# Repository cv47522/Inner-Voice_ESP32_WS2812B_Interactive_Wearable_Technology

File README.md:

# Inner Voice

- Wearable Technology and Functional Wear Study Project.
- Materials: ESP32 / Flora RGB Smart NeoPixel / Conductive Fabrics & Yarns
- Language: Arduino
- **More details of the project (Demo Video): https://wantinghsieh.com/inner-voice**

---

## Build

**[Link to the documentation page.](https://fabacademy.wantinghsieh.com/assignment/16-wildcard-week)**

## Belt Controller

## Bracelet Controller

## WS2812B Trianguler Light Modules

---

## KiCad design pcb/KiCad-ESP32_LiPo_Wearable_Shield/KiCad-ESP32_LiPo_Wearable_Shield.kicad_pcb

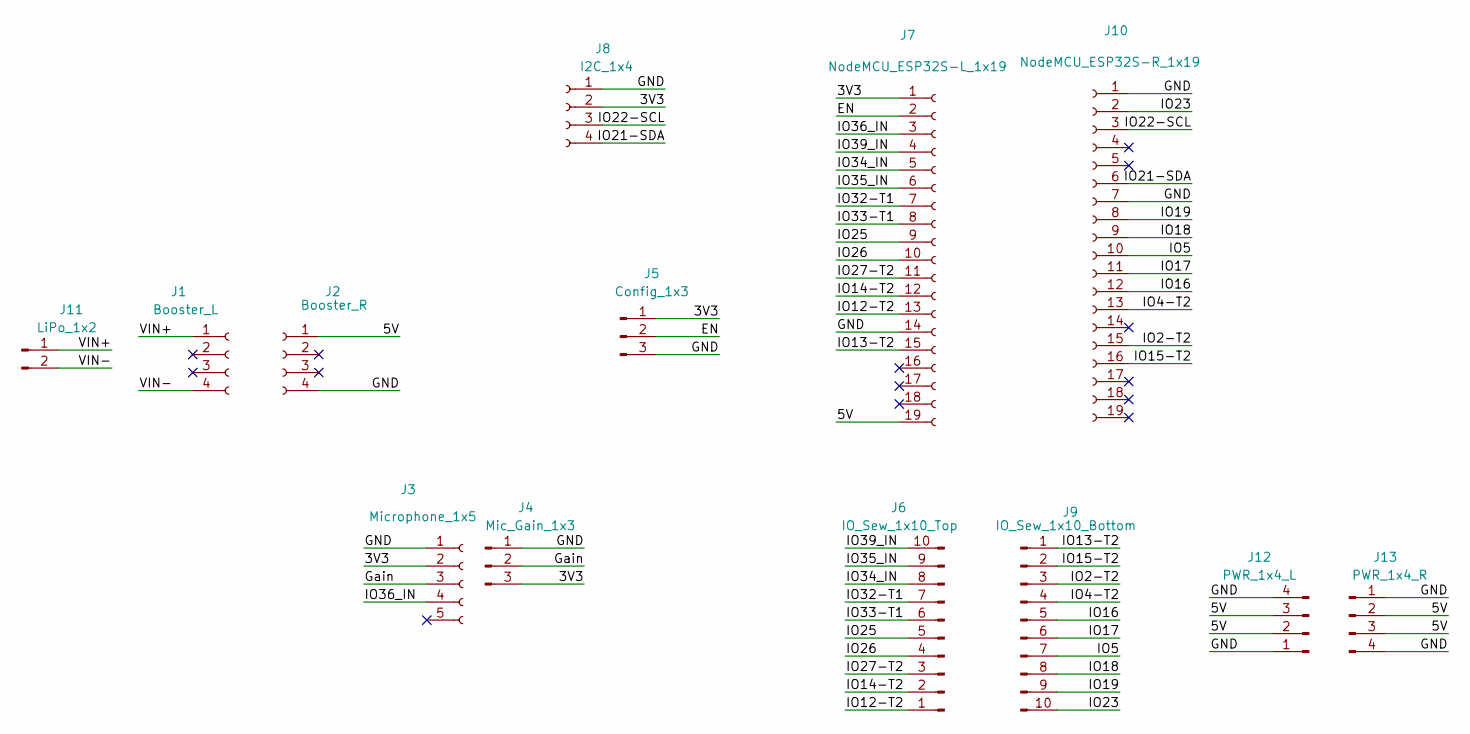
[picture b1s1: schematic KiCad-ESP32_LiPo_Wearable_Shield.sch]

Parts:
J1: Booster_L; PinHeader_1x04_P2.54mm_Vertical_SMD_Pin1Right
J2: Booster_R; PinHeader_1x04_P2.54mm_Vertical_SMD_Pin1Right
J3: Microphone_1x5; PinHeader_1x05_P2.54mm_Vertical_SMD_Pin1Left
J4: Mic_Gain_1x3; PinHeader_1x03_P2.54mm_Vertical_SMD_Pin1Right
J5: Config_1x3; PinHeader_1x03_P2.54mm_Vertical_SMD_Pin1Right
J6: IO_Sew_1x10_Top; PinHeader_1x10_P7mm_I3mm_Vertical
J7: NodeMCU_ESP32S-L_1x19; PinHeader_1x19_P2.54mm_Vertical_SMD_Pin1Right
J8: I2C_1x4; PinSocket_1x04_P2.54mm_Vertical_SMD_Pin1Left
J9: IO_Sew_1x10_Bottom; PinHeader_1x10_P7mm_I3mm_Vertical
J10: NodeMCU_ESP32S-R_1x19; PinHeader_1x19_P2.54mm_Vertical_SMD_Pin1Right
J11: LiPo_1x2; JST_PH_S2B-PH-K_1x02_P2.00mm_I1.5mm_Horizontal
J12: PWR_1x4_L; PinHeader_1x04_P7mm_I3mm_Vertical
J13: PWR_1x4_R; PinHeader_1x04_P7mm_I3mm_Vertical

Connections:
/3V3: J3.2, J4.3, J5.1, J7.1, J8.2
/5V: J2.1, J7.19, J12.2, J12.3, J13.2, J13.3
/EN: J5.2, J7.2
/GND: J2.4, J3.1, J4.1, J5.3, J7.14, J8.1, J10.1, J10.7, J12.1, J12.4, J13.1, J13.4
/Gain: J3.3, J4.2
/IO2-T2: J9.3, J10.15
/IO4-T2: J9.4, J10.13
/IO5: J9.7, J10.10
/IO12-T2: J6.1, J7.13
/IO13-T2: J7.15, J9.1
/IO14-T2: J6.2, J7.12
/IO15-T2: J9.2, J10.16
/IO16: J9.5, J10.12
/IO17: J9.6, J10.11
/IO18: J9.8, J10.9
/IO19: J9.9, J10.8
/IO21-SDA: J8.4, J10.6
/IO22-SCL: J8.3, J10.3
/IO23: J9.10, J10.2
/IO25: J6.5, J7.9
/IO26: J6.4, J7.10
/IO27-T2: J6.3, J7.11
/IO32-T1: J6.7, J7.7
/IO33-T1: J6.6, J7.8
/IO34_IN: J6.8, J7.5
/IO35_IN: J6.9, J7.6
/IO36_IN: J3.4, J7.3
/IO39_IN: J6.10, J7.4
/VIN+: J1.1, J11.1
/VIN-: J1.4, J11.2

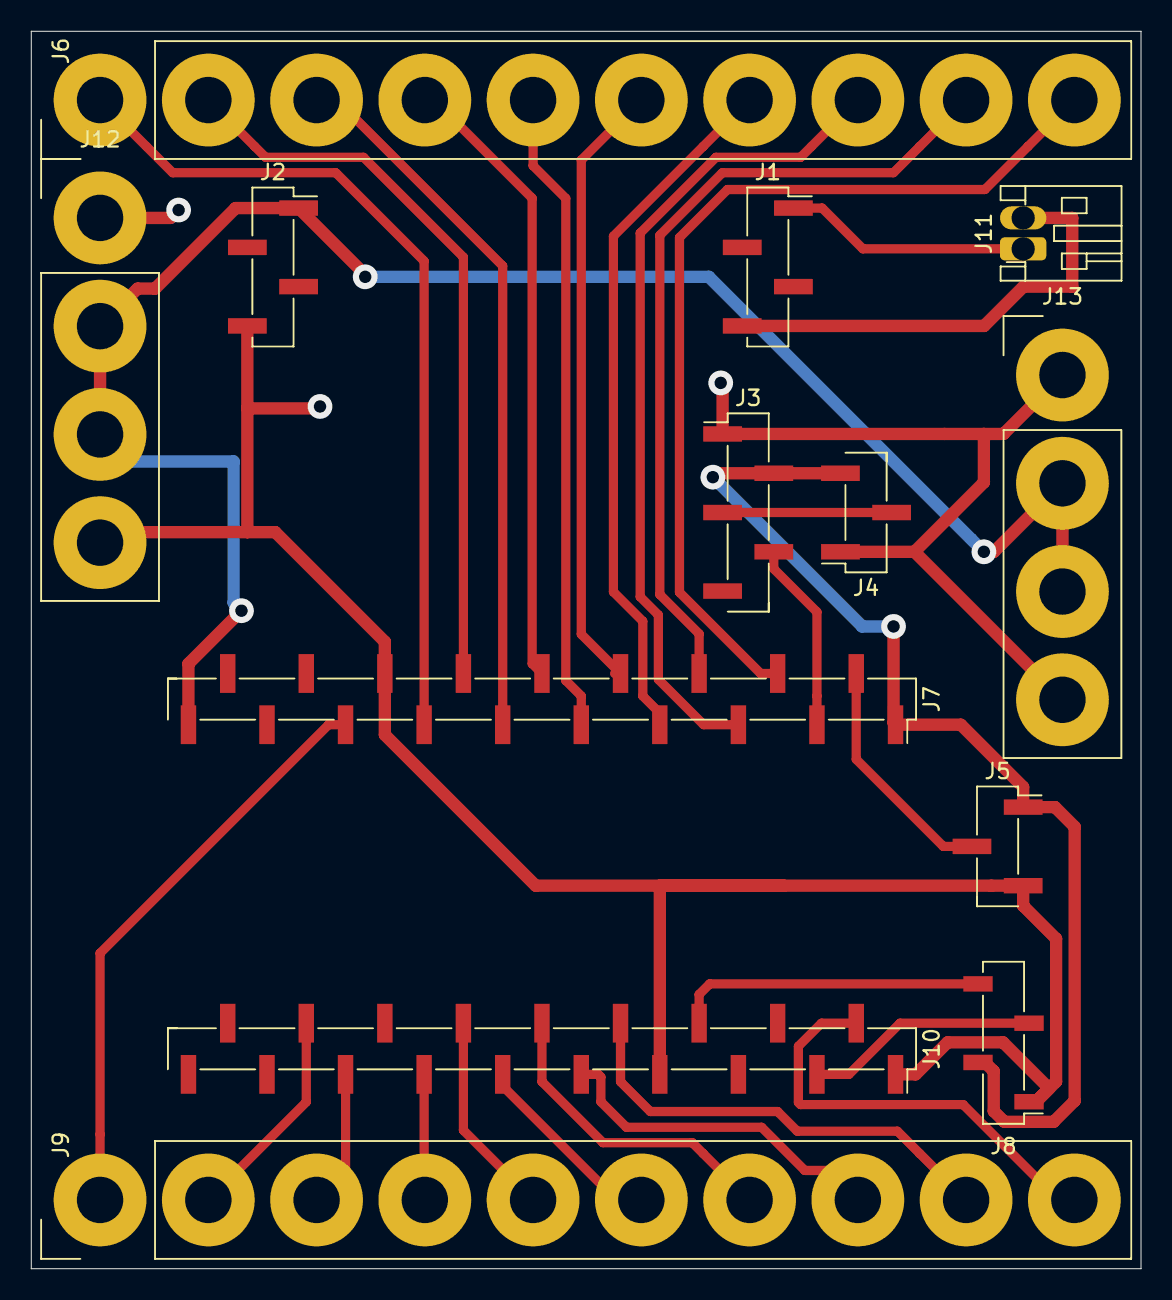
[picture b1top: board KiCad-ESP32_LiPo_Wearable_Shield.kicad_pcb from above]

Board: 2 copper layers, 71.8 x 80.0 mm, 13 parts (0 on the bottom side), 30 nets.

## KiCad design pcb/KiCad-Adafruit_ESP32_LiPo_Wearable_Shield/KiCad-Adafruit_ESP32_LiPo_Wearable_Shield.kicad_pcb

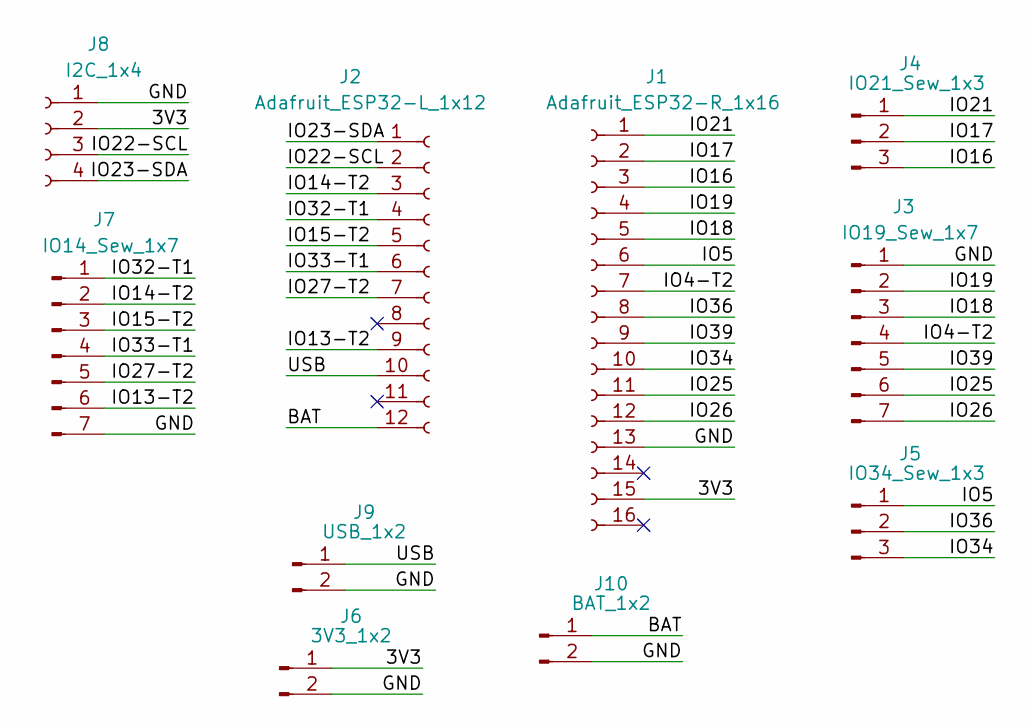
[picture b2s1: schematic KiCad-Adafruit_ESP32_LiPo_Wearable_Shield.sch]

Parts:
J1: Adafruit_ESP32-R_1x16; PinSocket_1x16_P2.54mm_Vertical_SMD_Pin1Right
J2: Adafruit_ESP32-L_1x12; PinSocket_1x12_P2.54mm_Vertical_SMD_Pin1Left
J3: IO19_Sew_1x7; PinHeader_1x07_P7mm_I3mm_Vertical
J4: IO21_Sew_1x3; PinHeader_1x03_P7mm_I3mm_Vertical
J5: IO34_Sew_1x3; PinHeader_1x03_P7mm_I3mm_Vertical
J6: 3V3_1x2; UPDI_Header_1x02_P2.54mm_Horizontal
J7: IO14_Sew_1x7; PinHeader_1x07_P7mm_I3mm_Vertical
J8: I2C_1x4; PinSocket_1x04_P2.54mm_Vertical_SMD_Pin1Left
J9: USB_1x2; UPDI_Header_1x02_P2.54mm_Horizontal
J10: BAT_1x2; UPDI_Header_1x02_P2.54mm_Horizontal

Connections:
/3V3: J1.15, J6.1, J8.2
/BAT: J2.12, J10.1
/GND: J1.13, J3.1, J6.2, J7.7, J8.1, J9.2, J10.2
/IO4-T2: J1.7, J3.4
/IO5: J1.6, J5.1
/IO13-T2: J2.9, J7.6
/IO14-T2: J2.3, J7.2
/IO15-T2: J2.5, J7.3
/IO16: J1.3, J4.3
/IO17: J1.2, J4.2
/IO18: J1.5, J3.3
/IO19: J1.4, J3.2
/IO21: J1.1, J4.1
/IO22-SCL: J2.2, J8.3
/IO23-SDA: J2.1, J8.4
/IO25: J1.11, J3.6
/IO26: J1.12, J3.7
/IO27-T2: J2.7, J7.5
/IO32-T1: J2.4, J7.1
/IO33-T1: J2.6, J7.4
/IO34: J1.10, J5.3
/IO36: J1.8, J5.2
/IO39: J1.9, J3.5
/USB: J2.10, J9.1

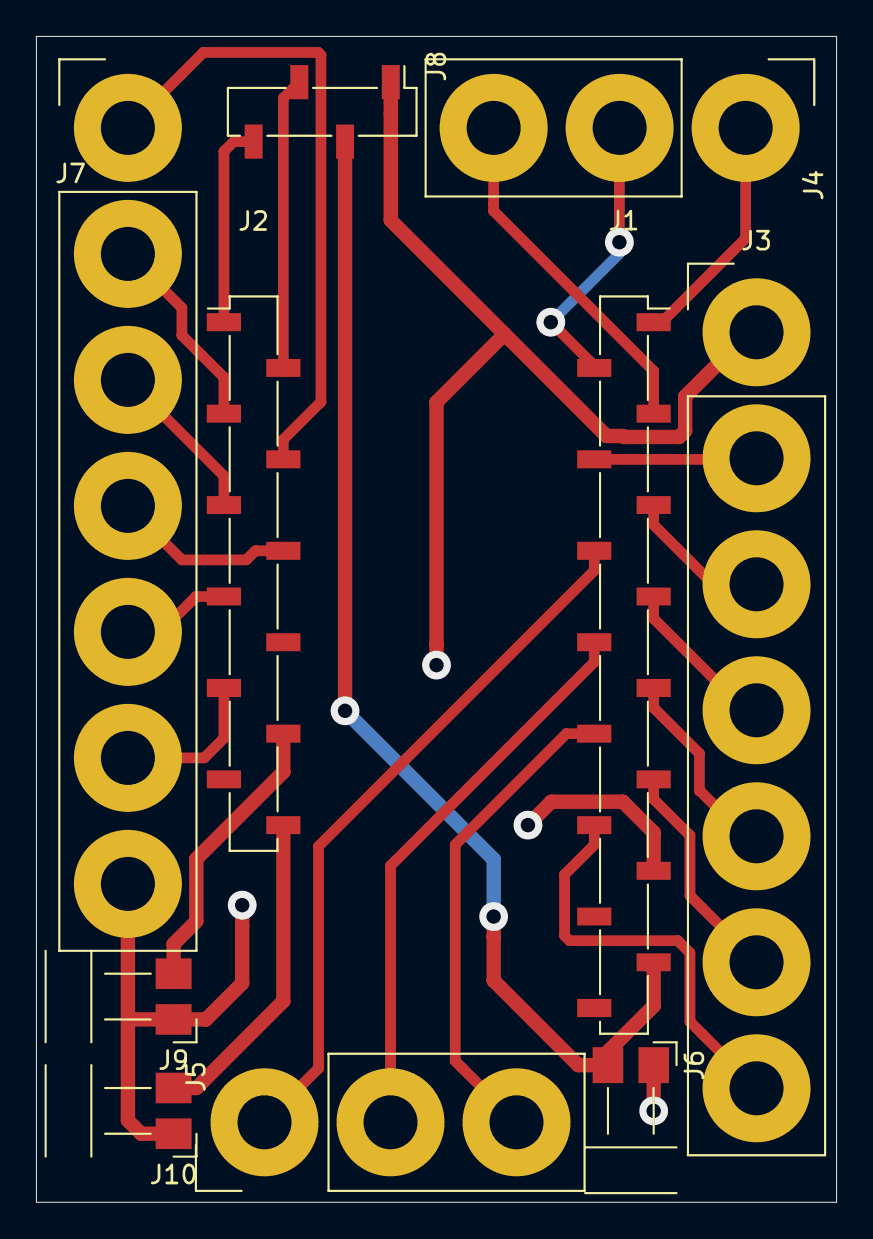
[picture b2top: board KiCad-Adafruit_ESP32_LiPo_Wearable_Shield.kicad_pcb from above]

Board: 2 copper layers, 44.4 x 64.8 mm, 10 parts (0 on the bottom side), 24 nets.

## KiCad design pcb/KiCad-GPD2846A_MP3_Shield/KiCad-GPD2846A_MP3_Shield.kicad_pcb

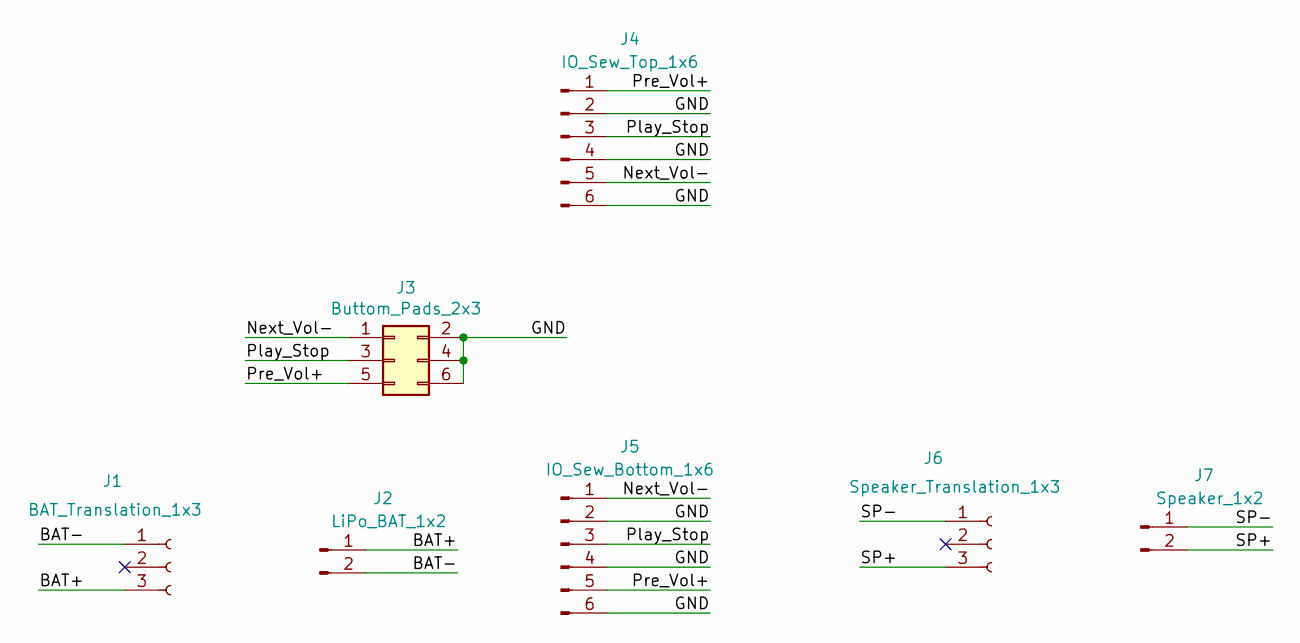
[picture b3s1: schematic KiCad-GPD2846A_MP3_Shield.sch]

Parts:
J1: BAT_Translation_1x3; Female_Header_1x03_P2.54mm_Horizontal
J2: LiPo_BAT_1x2; JST_PH_S2B-PH-K_1x02_P2.00mm_I1.5mm_Horizontal
J3: Buttom_Pads_2x3; PinHeader_2x03_P2.54mm_Vertical_SMD
J4: IO_Sew_Top_1x6; PinHeader_1x06_P7mm_I3mm_Vertical
J5: IO_Sew_Bottom_1x6; PinHeader_1x06_P7mm_I3mm_Vertical
J6: Speaker_Translation_1x3; Female_Header_1x03_P2.54mm_Horizontal
J7: Speaker_1x2; Term_Block_1x2_P5mm_I1.5mm

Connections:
/BAT+: J1.3, J2.1
/BAT-: J1.1, J2.2
/GND: J3.2, J3.4, J3.6, J4.2, J4.4, J4.6, J5.2, J5.4, J5.6
/Next_Vol-: J3.1, J4.5, J5.1
/Play_Stop: J3.3, J4.3, J5.3
/Pre_Vol+: J3.5, J4.1, J5.5
/SP+: J6.3, J7.2
/SP-: J6.1, J7.1

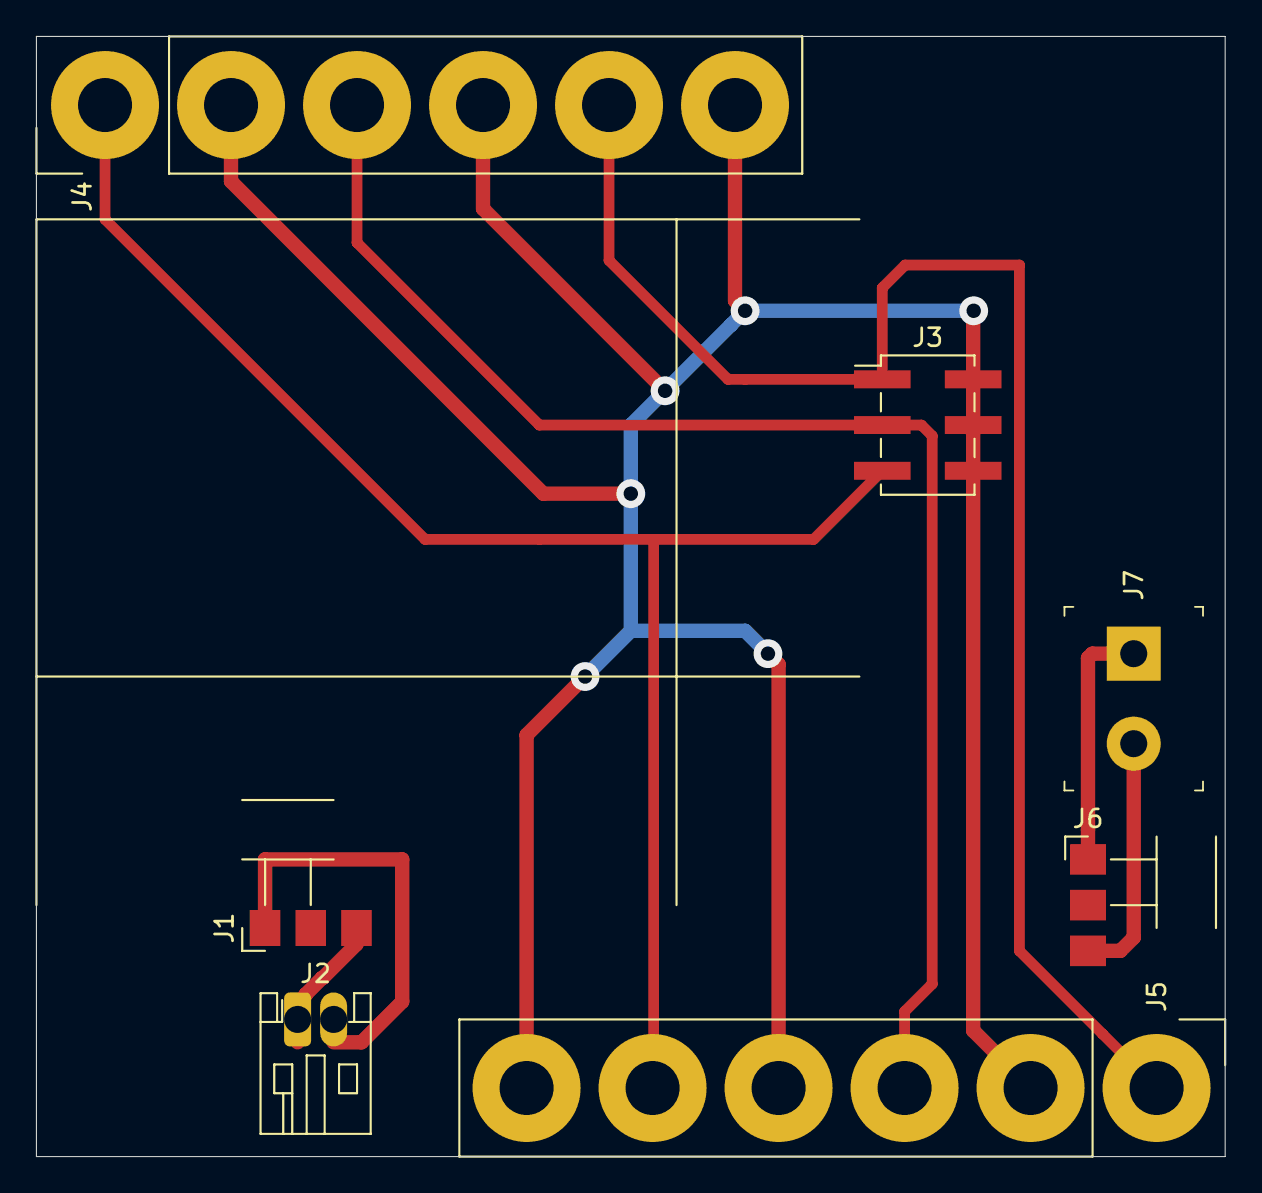
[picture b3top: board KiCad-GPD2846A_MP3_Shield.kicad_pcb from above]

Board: 2 copper layers, 66.0 x 62.2 mm, 7 parts (0 on the bottom side), 8 nets.

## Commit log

2020-11-11 Add .gitignore
